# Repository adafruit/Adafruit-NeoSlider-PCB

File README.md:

## Adafruit NeoSlider I2C QT Slide Potentiometer with 4 NeoPixels - STEMMA QT/QWIIC PCB

<a href="http://www.adafruit.com/products/5295"><br/>
Click here to purchase one from the Adafruit shop</a>

PCB files for the Adafruit NeoSlider I2C QT Slide Potentiometer with 4 NeoPixels - STEMMA QT/QWIIC. 

Format is EagleCAD schematic and board layout
* https://www.adafruit.com/product/5295

### Description

Our family of I2C-friendly user interface elements grows by one with this new product that makes it plug-n-play-easy to add a 75mm long slide potentiometer to any microcontroller or microcomputer with an I2C port.

Each breakout is 3" long and 0.8" wide, with a single linear slide pot in the center. Underneath, there are four under-lighting NeoPixels that can display any RGB color. In the middle, a small microcontroller takes I2C commands and converts them to analog reads (of the potentiometer) and NeoPixel control. Goes great with our Stemma QT rotary encoder and 1x4 NeoKey QT breakout.

Thanks to the Stemma QT / Qwiic connectors underneath, you can easily connect using QT cables - no soldering required! There's even four I2C selection jumpers that you can cut to change the address from the default 0x30 to any value up to 0x3F so up to 16 slide pots can all share one chained cable.

To get you going fast, we spun up a custom-made PCB with the seesaw chip and all supporting circuitry for 3 or 5V power and logic. The STEMMA QT connectors on either side are compatible with the SparkFun Qwiic I2C connectors. This allows you to make solderless connections between your development board and the rotary encoder or to chain them with a wide range of other sensors and accessories using a compatible cable. QT Cable is not included, but we have a variety in the shop.

You can use our Arduino library to control and read data with any compatible microcontroller. We also have CircuitPython/Python code for use with computers or single-board Linux boards.

### License

Adafruit invests time and resources providing this open source design, please support Adafruit and open-source hardware by purchasing products from [Adafruit](https://www.adafruit.com)!

Designed by Limor Fried/Ladyada for Adafruit Industries.

Creative Commons Attribution/Share-Alike, all text above must be included in any redistribution. 
See license.txt for additional details.

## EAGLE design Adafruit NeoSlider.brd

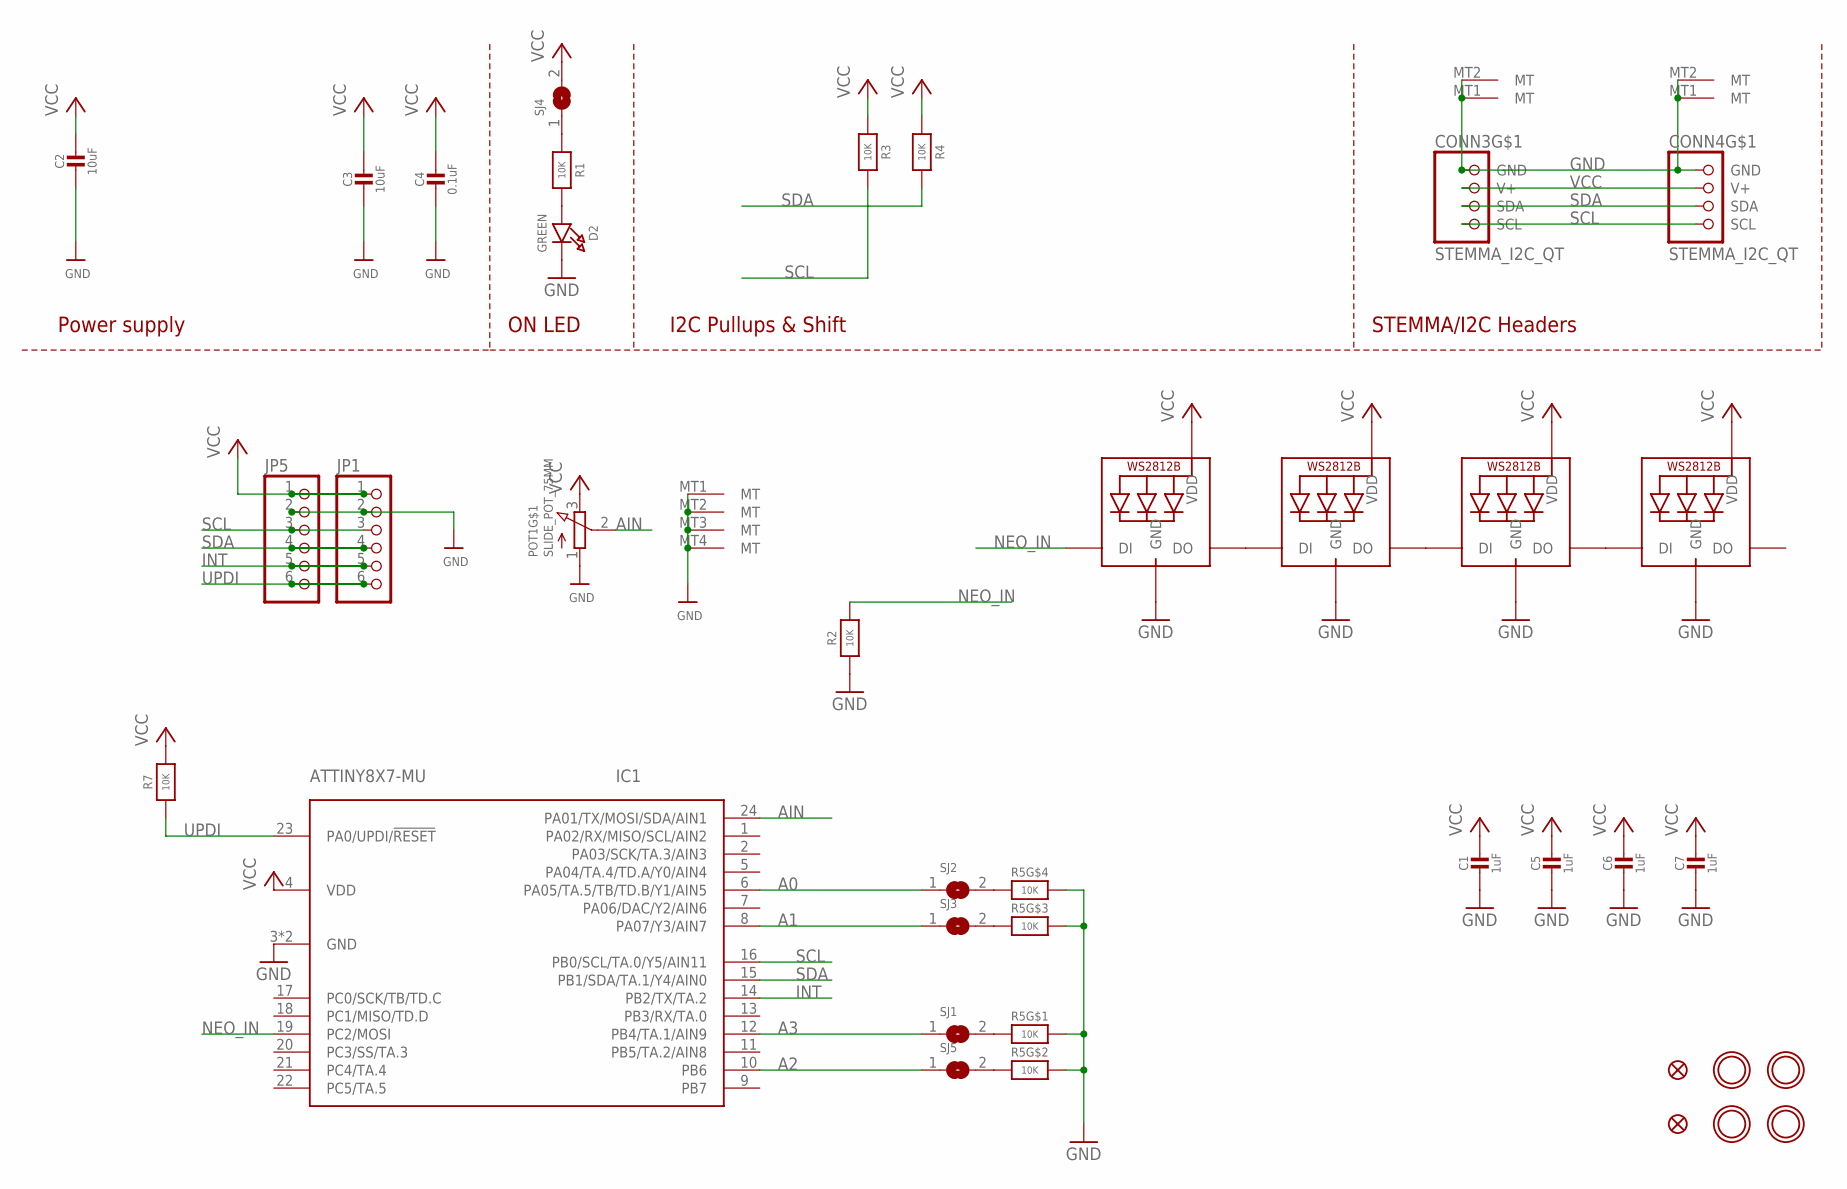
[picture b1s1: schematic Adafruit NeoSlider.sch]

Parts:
C1, C5, C6, C7: 1uF; 0603-NO
C2, C3: 10uF; 0805-NO
C4: 0.1uF; 0603-NO
CONN3, CONN4: STEMMA_I2C_QT; JST_SH4
D2: GREEN; CHIPLED_0603_NOOUTLINE
FID1, FID2: FIDUCIAL_1MM
IC1: ATTINY8X7-MU; QFN24_4MM
JP1, JP5: HEADER-1X670MIL; 1X06_ROUND_70
LED1, LED2, LED3, LED4: WS2812B_SK6812E; NEO3535_REVERSE
POT1: SLIDE_POT_75MM
R1, R2, R3, R4, R7: 10K; 0603-NO
R5: 10K; RESPACK_4X0603
SJ1, SJ2, SJ3, SJ4, SJ5: SOLDERJUMPERCLOSED; SOLDERJUMPER_CLOSEDWIRE
U$3, U$17, U$19, U$21: MOUNTINGHOLE2.5; MOUNTINGHOLE_2.5_PLATED

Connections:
A0: IC1.6 (PA05/TA.5/TB/TD.B/Y1/AIN5), SJ2.1
A1: IC1.8 (PA07/Y3/AIN7), SJ3.1
A2: IC1.10 (PB6), SJ5.1
A3: IC1.12 (PB4/TA.1/AIN9), SJ1.1
AIN: IC1.24 (PA01/TX/MOSI/SDA/AIN1), POT1.2 (S)
GND: C1.2, C2.2, C3.2, C4.2, C5.2, C6.2, C7.2, CONN3.1 (GND), CONN3.MT1 (MT), CONN3.MT2 (MT), CONN4.1 (GND), CONN4.MT1 (MT), CONN4.MT2 (MT), D2.C, IC1.3 (GND), IC1.THERM (GND), JP1.2, JP5.2, LED1.3-GND (GND), LED2.3-GND (GND), LED3.3-GND (GND), LED4.3-GND (GND), POT1.1 (A), POT1.MT1 (MT), POT1.MT2 (MT), POT1.MT3 (MT), POT1.MT4 (MT), R2.1, R5.5 (2), R5.6 (2), R5.7 (2), R5.8 (2)
INT: IC1.14 (PB2/TX/TA.2), JP1.5, JP5.5
unnamed: D2.A, R1.2
unnamed: LED1.2-DOUT (DO), LED2.4-DIN (DI)
unnamed: LED2.2-DOUT (DO), LED3.4-DIN (DI)
unnamed: LED3.2-DOUT (DO), LED4.4-DIN (DI)
unnamed: R5.1, SJ1.2
unnamed: R5.2 (1), SJ5.2
unnamed: R5.3 (1), SJ3.2
unnamed: R5.4 (1), SJ2.2
unnamed: R1.1, SJ4.1
NEO_IN: IC1.19 (PC2/MOSI), LED1.4-DIN (DI), R2.2
SCL: CONN3.4 (SCL), CONN4.4 (SCL), IC1.16 (PB0/SCL/TA.0/Y5/AIN11), JP1.3, JP5.3, R3.2
SDA: CONN3.3 (SDA), CONN4.3 (SDA), IC1.15 (PB1/SDA/TA.1/Y4/AIN0), JP1.4, JP5.4, R4.2
UPDI: IC1.23 (PA0/UPDI/!RESET), JP1.6, JP5.6, R7.1
VCC: C1.1, C2.1, C3.1, C4.1, C5.1, C6.1, C7.1, CONN3.2 (V+), CONN4.2 (V+), IC1.4 (VDD), JP1.1, JP5.1, LED1.1-VDD (VDD), LED2.1-VDD (VDD), LED3.1-VDD (VDD), LED4.1-VDD (VDD), POT1.3 (E), R3.1, R4.1, R7.2, SJ4.2

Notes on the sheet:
I2C Pullups & Shift
STEMMA/I2C Headers
ON LED
Power supply

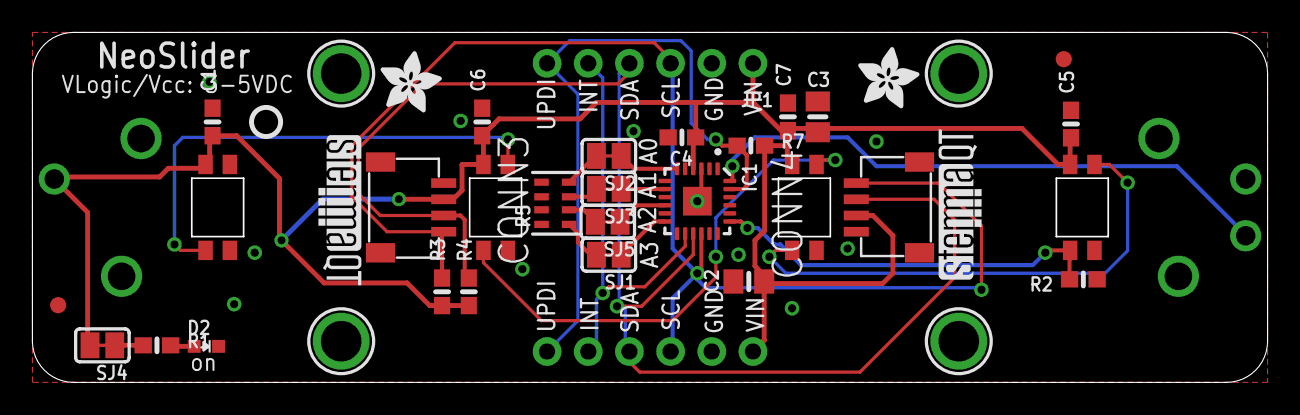
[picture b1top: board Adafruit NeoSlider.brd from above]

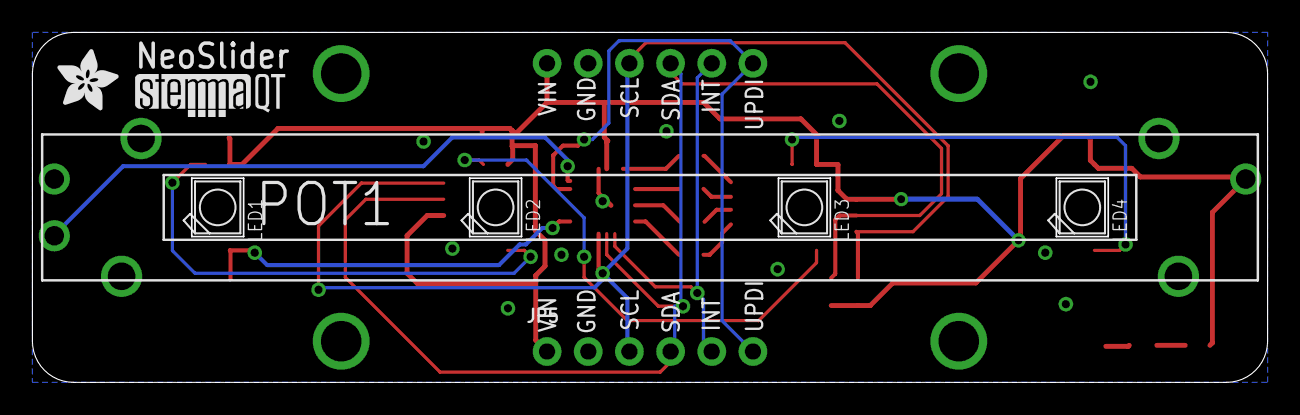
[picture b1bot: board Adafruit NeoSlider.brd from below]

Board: 2 copper layers, 76.1 x 21.5 mm, 42 parts (8 on the bottom side), 21 nets.

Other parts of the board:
U$1, U$2, U$9: ADAFRUIT_3.5MM
U$7, U$30, U$31: STEMMAQT
U$25: PCBFEAT-REV-040

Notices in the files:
parts and their libraries:
microbuilder: This work is placed in the public domain, and may be freely used for commercial and non-commercial work with the following conditions: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
